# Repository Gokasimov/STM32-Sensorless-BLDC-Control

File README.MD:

# Sensorless BLDC Motor Controller (STM32G431RBT6)

## 📌 Overview
This repository contains the complete hardware and firmware design for a **Sensorless 6-Step Trapezoidal BLDC Motor Controller** built around the STM32G4 microcontroller. The project demonstrates advanced embedded motor control techniques, including Back-EMF (BEMF) Zero-Crossing Detection (ZCD) via Injected ADCs, hardware-synchronized timers, and a custom-tuned PI speed controller.

The hardware was designed from scratch (KiCad) and tested rigorously to evaluate both physical limits (Voltage Saturation/Kv limits) and embedded software constraints (Timer Quantization limits).

---

## ⚙️ Firmware Architecture & Control Theory

The firmware avoids blocking delays and polling. It relies entirely on a deterministic, interrupt-driven architecture utilizing STM32 Advanced Timers and ADC peripherals.

### 1. Robust State-Machine
The motor control flow is managed by a strict state machine to ensure safe start-up and running conditions:
* **IDLE:** PWM outputs are disabled (Soft Stop / Coasting).
* **ALIGN:** A static DC magnetic field is applied to the stator to force the mechanical rotor into a known starting position.
* **RAMP-UP:** Open-loop commutation with progressively decreasing delay to generate enough initial BEMF for the ADCs to read.
* **CLOSED-LOOP:** Sensorless commutation takes over. The system relies purely on ZCD events and the PI controller manages the PWM duty cycle to reach the target RPM.
* **FAULT:** Emergency hard-stop triggered by stall detection or hardware limits.

### 2. Injected ADC & Timer Synchronization
To avoid high-frequency PWM switching noise (ringing), BEMF is **not** polled continuously in the main loop. Instead, the STM32's **Injected ADC** channels are hardware-triggered by `TIM1`'s Update/Compare events. 
This ensures that the BEMF voltage is sampled exactly at the optimal moment (typically the PWM ON state or center-aligned peak), providing a clean signal for the ZCD algorithm without requiring heavy software filtering.

### 3. PI Speed Control & Super-Sampling (MAF)
Speed calculation at high RPMs suffers from timer resolution limits (Quantization Error). To mitigate this without using floating-point math on every cycle, a **Moving Average Filter (MAF)** is implemented.
The PI controller runs deterministically in a dedicated 1kHz timer interrupt (`TIM7`). It compares the filtered RPM against the target and smoothly adjusts the duty cycle, featuring anti-windup clamping to protect the system.

---

## 🔬 Key Hardware Verifications

Theoretical models were strictly validated against physical hardware behavior using a 4-channel oscilloscope and RAM data logging. *(For full oscilloscope captures, including Dead-Time verification, please see the [Results/](./Results) folder).*

### 1. Hardware RC Filter Phase Shift & ZCD Smoothing

> **Analysis:** The Yellow trace shows the raw Phase 1 voltage. The Blue trace shows the signal at the STM32 ADC pin after the resistor divider and RC filter. The filter successfully eliminates PWM noise. Crucially, the inherent RC time delay acts as a natural "Phase Advance," optimizing high-speed commutation timing directly in hardware, eliminating the need for 30-degree software compensation.

### 2. System Limit Discovery (RAM Datalogging)

> **Analysis (Step Response & Limitations):** Extracted via an 8KB internal RAM "Flight Recorder" to avoid UART bottlenecking. The graph reveals two physical realities:
> * **Voltage Saturation:** The PI controller pushes the Duty Cycle (Green) to its ~95% limit to reach 14200 RPM, but the motor plateaus at ~9500 RPM (Orange). The motor has hit its BEMF ceiling for a 12V supply ($\Delta V \approx 0$).
> * **Quantization Artifacts:** The step-like jumps at peak speeds are not physical. They are artifacts of the 50us timer resolution; at extreme speeds, a 1-tick variation in commutation measurement results in massive calculated RPM swings, proving the necessity of the MAF implemented in the code.

---

## 🔌 Quick Start & Hardware Setup

### Custom Hardware Notes (v1.0 Prototyping)
* **MP1482 Bypass:** Due to a layout errata on the v1.0 PCB, the onboard 12V-to-3.3V buck converter is bypassed. Logic power is supplied externally. (See `Hardware/ERRATA.md` for details).
* **Future-Proofing (DNP):** The board includes footprints for inline current shunts, op-amps, and encoder headers. These are currently marked as DNP (Do Not Populate) as they are reserved for the upcoming FOC (Field Oriented Control) revision.

## 📁 Repository Structure

📦 STM32-Sensorless-BLDC-Control
 ┣ 📂 Firmware         # STM32CubeIDE Project (C source, headers, .ioc)
 ┣ 📂 Hardware         # KiCad project, Schematics (PDF), BOM, and Errata
 ┣ 📂 Results          # Oscilloscope captures and Step Response graphs
 ┣ 📜 .gitignore       # Excludes IDE debug/build binaries
 ┣ 📜 README.md        # You are here
 ┗ 📜 LICENSE          # MIT License

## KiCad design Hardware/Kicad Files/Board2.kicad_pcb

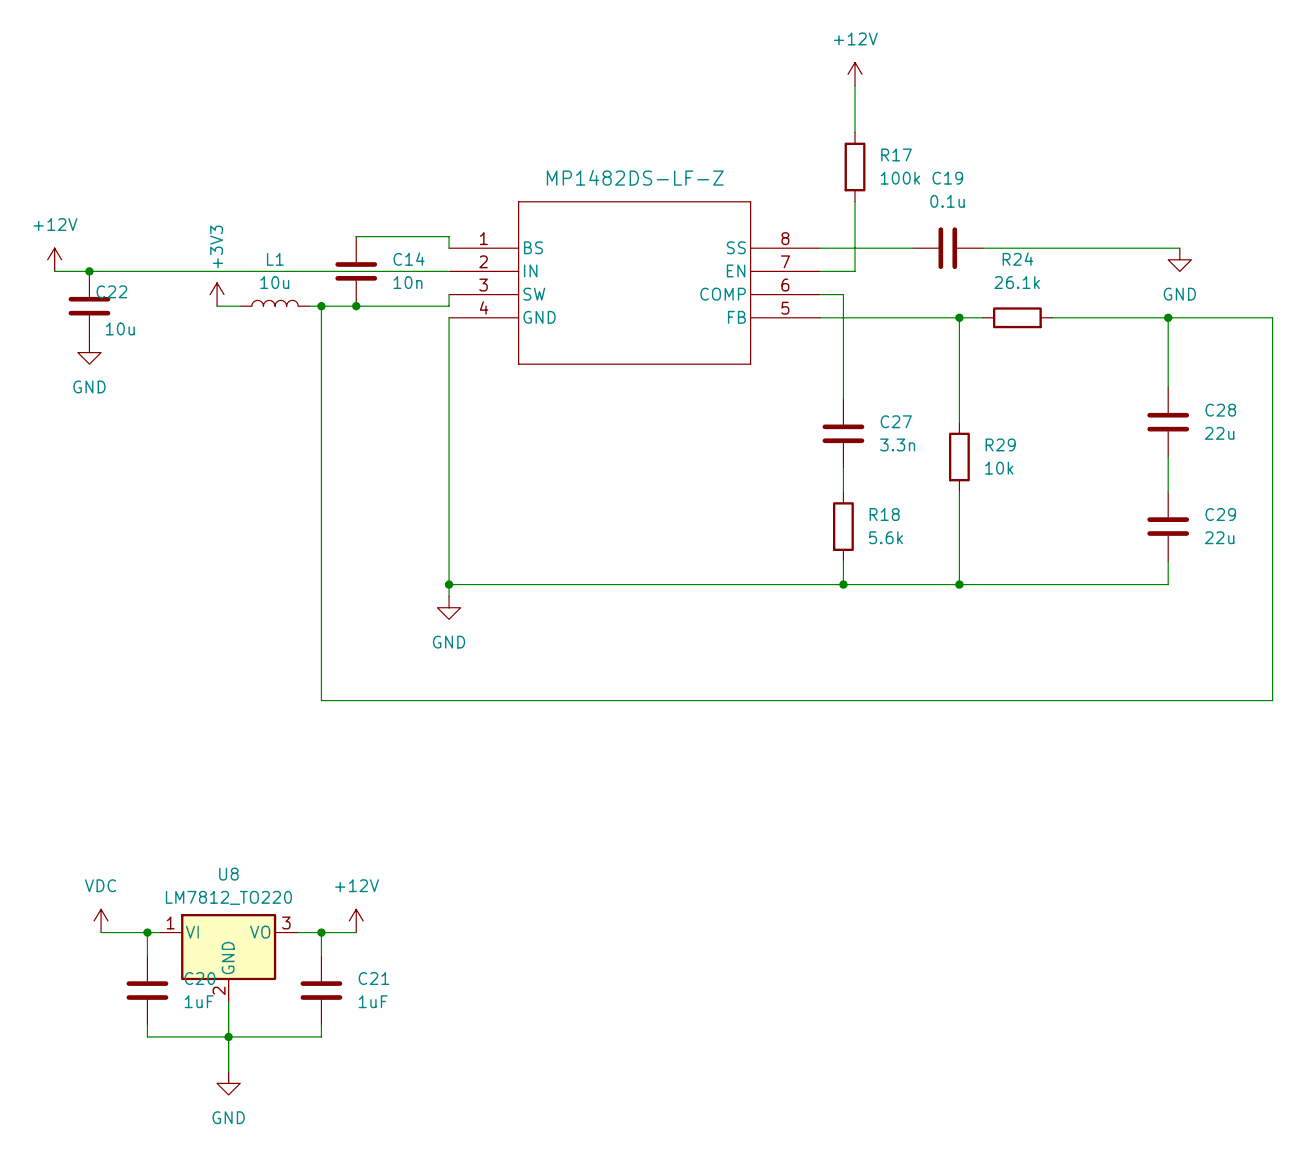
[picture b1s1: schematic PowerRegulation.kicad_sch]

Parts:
C14: 10n; C_0805_2012Metric
C19: 0.1u; C_0805_2012Metric
C20, C21: 1uF; C_0805_2012Metric
C22: 10u; C_0805_2012Metric
C27: 3.3n; C_0805_2012Metric
C28, C29: 22u; C_0805_2012Metric
L1: 10u; L_7.3x7.3_H3.5
R17: 100k; R_0805_2012Metric
R18: 5.6k; R_0805_2012Metric
R24: 26.1k; R_0805_2012Metric
R29: 10k; R_0805_2012Metric
U7: MP1482DS-LF-Z; SOIC-8_3.9x4.9mm_P1.27mm
U8: LM7812_TO220; TO-220-3_Vertical

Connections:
+3V3: L1.1; also elsewhere on the board
+12V: C21.1, C22.2, R17.1, U7.2 (IN), U8.3 (VO); also elsewhere on the board
GND: C19.2, C20.2, C21.2, C22.1, C29.1, R18.2, R29.2, U7.4 (GND), U8.2 (GND); also elsewhere on the board
unnamed: C27.1, R18.1
unnamed: C28.1, C29.2
unnamed: C14.1, U7.1 (BS)
unnamed: C27.2, U7.6 (COMP)
unnamed: R17.2, U7.7 (EN)
unnamed: R24.1, R29.1, U7.5 (FB)
unnamed: C19.1, U7.8 (SS)
unnamed: C14.2, C28.2, L1.2, R24.2, U7.3 (SW)
VDC: C20.1, U8.1 (VI); also elsewhere on the board

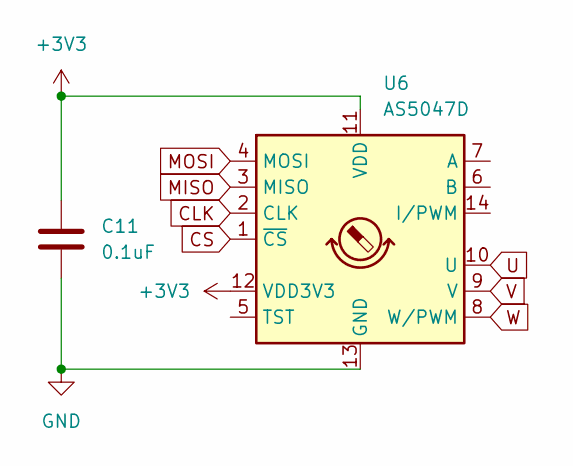
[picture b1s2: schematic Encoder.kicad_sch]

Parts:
C11: 0.1uF; C_0805_2012Metric
U6: AS5047D; TSSOP-14_4.4x5mm_P0.65mm

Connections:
+3V3: C11.1, U6.11 (VDD), U6.12 (VDD3V3); also elsewhere on the board
CLK: U6.2 (CLK); also elsewhere on the board
CS: U6.1 (~CS); also elsewhere on the board
GND: C11.2, U6.13 (GND); also elsewhere on the board
MISO: U6.3 (MISO); also elsewhere on the board
MOSI: U6.4 (MOSI); also elsewhere on the board
U: U6.10 (U); also elsewhere on the board
V: U6.9 (V); also elsewhere on the board
W: U6.8 (W/PWM); also elsewhere on the board

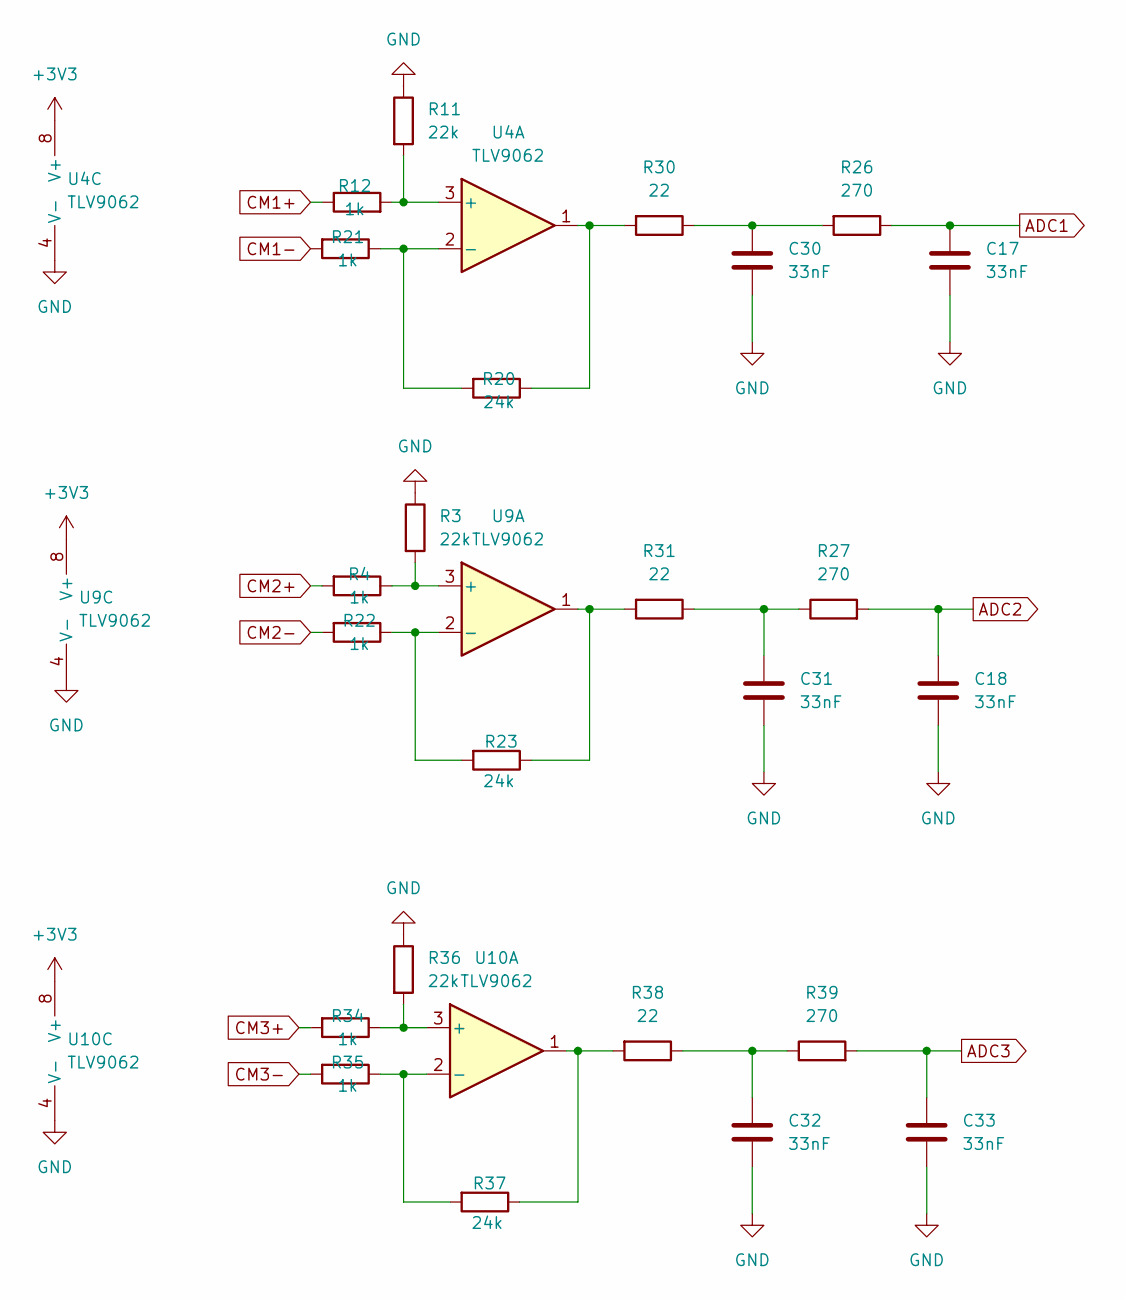
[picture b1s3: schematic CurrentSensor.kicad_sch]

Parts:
C17, C18, C30, C31, C32, C33: 33nF; C_0805_2012Metric
R3, R11, R36: 22k; R_0805_2012Metric
R4, R12, R21, R22, R34, R35: 1k; R_0805_2012Metric
R20, R23, R37: 24k; R_0805_2012Metric
R26, R27, R39: 270; R_0805_2012Metric
R30, R31, R38: 22; R_0805_2012Metric
U4, U9, U10: TLV9062; SOIC-8_3.9x4.9mm_P1.27mm

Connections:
+3V3: U4.8 (V+), U9.8 (V+), U10.8 (V+); also elsewhere on the board
ADC1: C17.1, R26.1; also elsewhere on the board
ADC2: C18.2, R27.2; also elsewhere on the board
ADC3: C33.2, R39.2
CM1+: R12.1; also elsewhere on the board
CM1-: R21.2; also elsewhere on the board
CM2+: R4.2; also elsewhere on the board
CM2-: R22.2; also elsewhere on the board
CM3+: R34.2; also elsewhere on the board
CM3-: R35.2; also elsewhere on the board
GND: C17.2, C18.1, C30.2, C31.2, C32.2, C33.1, R3.1, R11.1, R36.1, U4.4 (V-), U9.4 (V-), U10.4 (V-); also elsewhere on the board
unnamed: C30.1, R26.2, R30.1
unnamed: C31.1, R27.1, R31.1
unnamed: C32.1, R38.1, R39.1
unnamed: R20.1, R30.2, U4.1
unnamed: R23.1, R31.2, U9.1
unnamed: R37.1, R38.2, U10.1
unnamed: R11.2, R12.2, U4.3 (+)
unnamed: R20.2, R21.1, U4.2 (-)
unnamed: R3.2, R4.1, U9.3 (+)
unnamed: R22.1, R23.2, U9.2 (-)
unnamed: R34.1, R36.2, U10.3 (+)
unnamed: R35.1, R37.2, U10.2 (-)

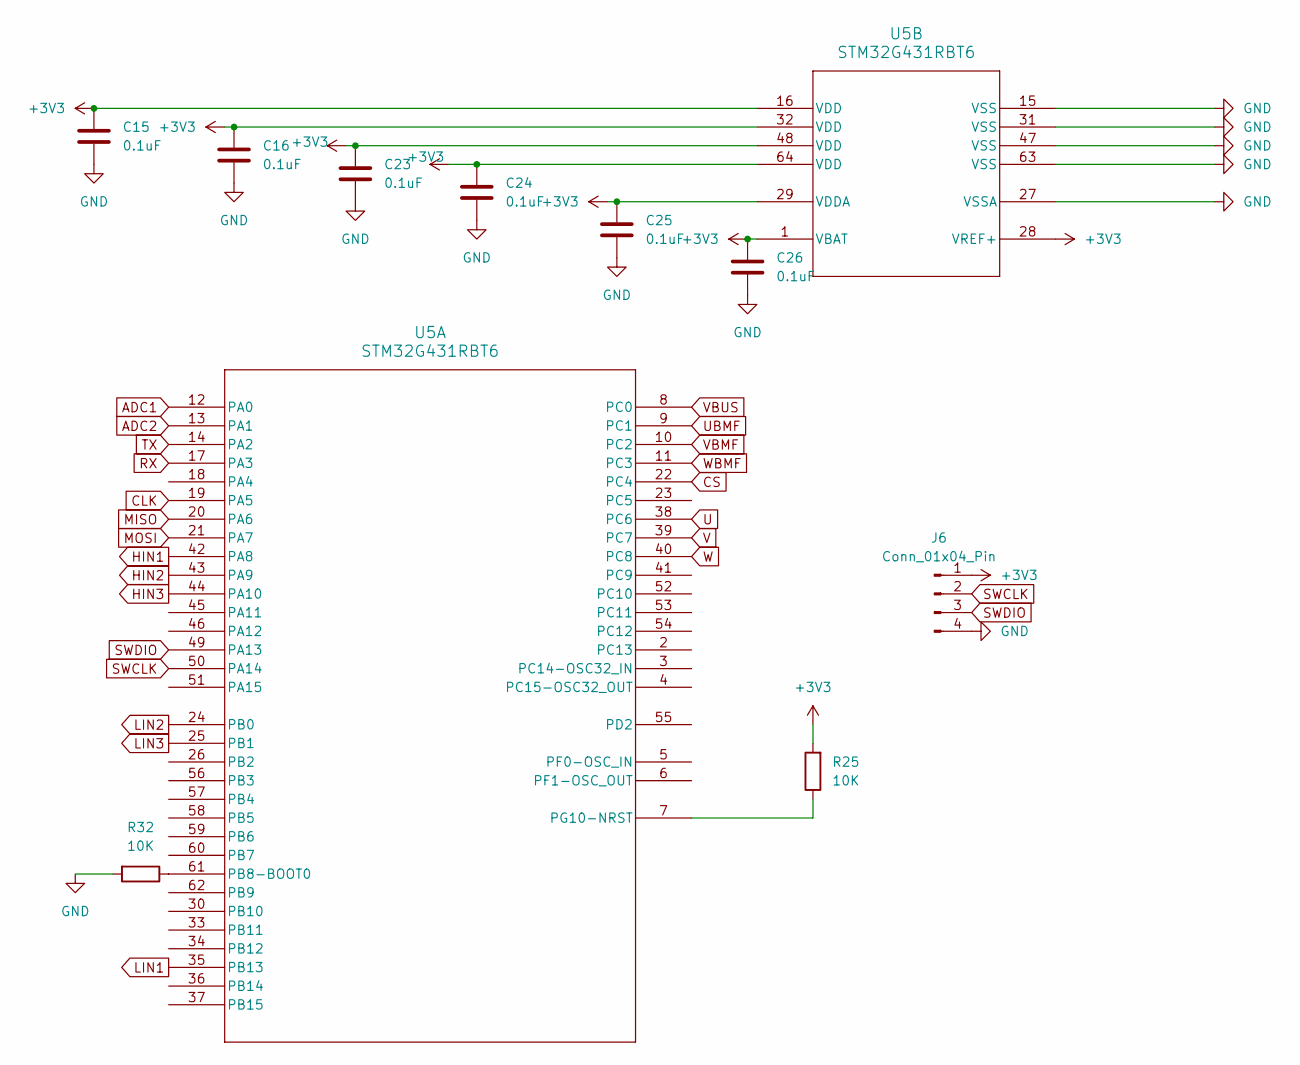
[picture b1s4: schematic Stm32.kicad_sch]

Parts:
C15, C16, C23, C24, C25, C26: 0.1uF; C_0805_2012Metric
J6: Conn_01x04_Pin; PinHeader_1x04_P2.54mm_Vertical
R25, R32: 10K; R_0805_2012Metric
U5: STM32G431RBT6; LQFP-64_10x10mm_P0.5mm

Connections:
+3V3: C15.1, C16.1, C23.1, C24.1, C25.1, C26.1, J6.1, R25.2, U5.1 (VBAT), U5.16 (VDD), U5.28 (VREF+), U5.29 (VDDA), U5.32 (VDD), U5.48 (VDD), U5.64 (VDD); also elsewhere on the board
ADC1: U5.12 (PA0); also elsewhere on the board
ADC2: U5.13 (PA1); also elsewhere on the board
CLK: U5.19 (PA5); also elsewhere on the board
CS: U5.22 (PC4); also elsewhere on the board
GND: C15.2, C16.2, C23.2, C24.2, C25.2, C26.2, J6.4, R32.2, U5.15 (VSS), U5.27 (VSSA), U5.31 (VSS), U5.47 (VSS), U5.63 (VSS); also elsewhere on the board
HIN1: U5.42 (PA8); also elsewhere on the board
HIN2: U5.43 (PA9); also elsewhere on the board
HIN3: U5.44 (PA10); also elsewhere on the board
LIN1: U5.35 (PB13); also elsewhere on the board
LIN2: U5.24 (PB0); also elsewhere on the board
LIN3: U5.25 (PB1); also elsewhere on the board
MISO: U5.20 (PA6); also elsewhere on the board
MOSI: U5.21 (PA7); also elsewhere on the board
unnamed: R32.1, U5.61 (PB8-BOOT0)
unnamed: R25.1, U5.7 (PG10-NRST)
RX: U5.17 (PA3)
SWCLK: J6.2, U5.50 (PA14)
SWDIO: J6.3, U5.49 (PA13)
TX: U5.14 (PA2)
U: U5.38 (PC6); also elsewhere on the board
UBMF: U5.9 (PC1); also elsewhere on the board
V: U5.39 (PC7); also elsewhere on the board
VBMF: U5.10 (PC2); also elsewhere on the board
VBUS: U5.8 (PC0); also elsewhere on the board
W: U5.40 (PC8); also elsewhere on the board
WBMF: U5.11 (PC3); also elsewhere on the board

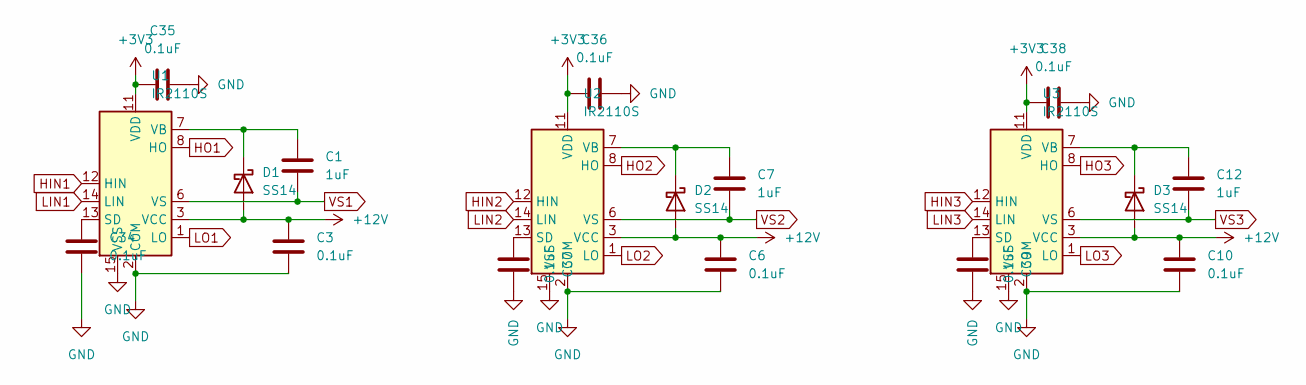
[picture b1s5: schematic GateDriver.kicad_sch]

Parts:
C1, C7, C12: 1uF; C_0805_2012Metric
C3, C6, C10, C34, C35, C36, C37, C38, C39: 0.1uF; C_0805_2012Metric
D1, D2, D3: SS14; D_SMA
U1, U2, U3: IR2110S; SOIC-16W_7.5x10.3mm_P1.27mm

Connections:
+3V3: C35.1, C36.1, C38.1, U1.11 (VDD), U2.11 (VDD), U3.11 (VDD); also elsewhere on the board
+12V: C3.1, C6.1, C10.1, D1.2 (A), D2.2 (A), D3.2 (A), U1.3 (VCC), U2.3 (VCC), U3.3 (VCC); also elsewhere on the board
GND: C3.2, C6.2, C10.2, C34.2, C35.2, C36.2, C37.2, C38.2, C39.2, U1.2 (COM), U1.15 (VSS), U2.2 (COM), U2.15 (VSS), U3.2 (COM), U3.15 (VSS); also elsewhere on the board
HIN1: U1.12 (HIN); also elsewhere on the board
HIN2: U2.12 (HIN); also elsewhere on the board
HIN3: U3.12 (HIN); also elsewhere on the board
HO1: U1.8 (HO); also elsewhere on the board
HO2: U2.8 (HO); also elsewhere on the board
HO3: U3.8 (HO); also elsewhere on the board
LIN1: U1.14 (LIN); also elsewhere on the board
LIN2: U2.14 (LIN); also elsewhere on the board
LIN3: U3.14 (LIN); also elsewhere on the board
LO1: U1.1 (LO); also elsewhere on the board
LO2: U2.1 (LO); also elsewhere on the board
LO3: U3.1 (LO); also elsewhere on the board
unnamed: C1.1, D1.1 (K), U1.7 (VB)
unnamed: C7.1, D2.1 (K), U2.7 (VB)
unnamed: C12.1, D3.1 (K), U3.7 (VB)
unnamed: C34.1, U1.13 (SD)
unnamed: C37.1, U2.13 (SD)
unnamed: C39.1, U3.13 (SD)
VS1: C1.2, U1.6 (VS); also elsewhere on the board
VS2: C7.2, U2.6 (VS); also elsewhere on the board
VS3: C12.2, U3.6 (VS); also elsewhere on the board

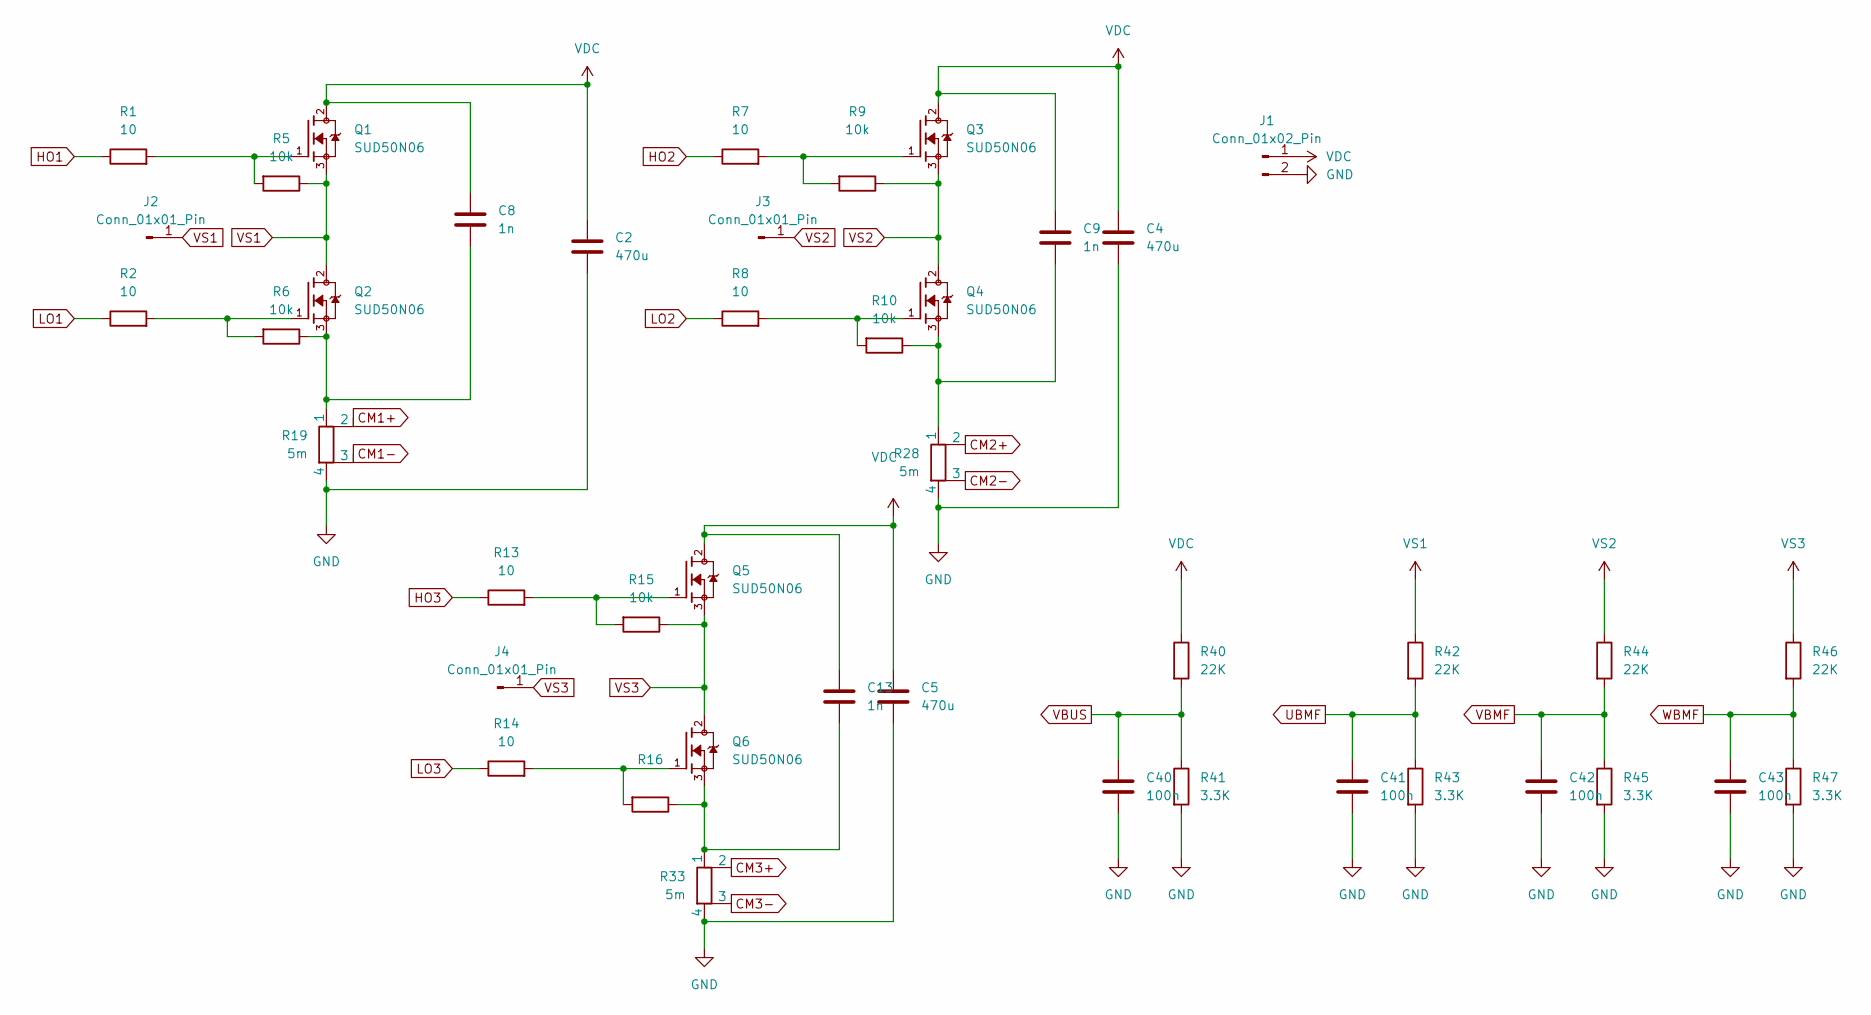
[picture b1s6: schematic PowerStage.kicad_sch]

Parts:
C2, C4, C5: 470u; CP_Radial_D10.0mm_P5.00mm
C8, C9, C13: 1n; C_0805_2012Metric
C40, C41, C42, C43: 100n; C_0805_2012Metric
J1: Conn_01x02_Pin; AMASS_XT60-M_1x02_P7.20mm_Vertical
J2, J3, J4: Conn_01x01_Pin; SolderWire-2sqmm_1x01_D2mm_OD3.9mm
Q1, Q2, Q3, Q4, Q5, Q6: SUD50N06; TO-252-2
R1, R2, R7, R8, R13, R14: 10; R_0805_2012Metric
R5, R6, R9, R10, R15, R16: 10k; R_0805_2012Metric
R19, R28, R33: 5m; R_Shunt_Vishay_WSK2512_6332Metric_T1.19mm
R40, R42, R44, R46: 22K; R_0805_2012Metric
R41, R43, R45, R47: 3.3K; R_0805_2012Metric

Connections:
CM1+: R19.2; also elsewhere on the board
CM1-: R19.3; also elsewhere on the board
CM2+: R28.2; also elsewhere on the board
CM2-: R28.3; also elsewhere on the board
CM3+: R33.2; also elsewhere on the board
CM3-: R33.3; also elsewhere on the board
GND: C2.2, C4.2, C5.2, C40.2, C41.2, C42.2, C43.2, J1.2, R19.4, R28.4, R33.4, R41.2, R43.2, R45.2, R47.2; also elsewhere on the board
HO1: R1.1; also elsewhere on the board
HO2: R7.1; also elsewhere on the board
HO3: R13.1; also elsewhere on the board
LO1: R2.1; also elsewhere on the board
LO2: R8.1; also elsewhere on the board
LO3: R14.1; also elsewhere on the board
unnamed: C8.2, Q2.3, R6.1, R19.1
unnamed: C9.2, Q4.3, R10.1, R28.1
unnamed: C13.2, Q6.3, R16.1, R33.1
unnamed: Q1.1, R1.2, R5.2
unnamed: Q2.1, R2.2, R6.2
unnamed: Q3.1, R7.2, R9.2
unnamed: Q4.1, R8.2, R10.2
unnamed: Q5.1, R13.2, R15.2
unnamed: Q6.1, R14.2, R16.2
UBMF: C41.1, R42.2, R43.1; also elsewhere on the board
VBMF: C42.1, R44.2, R45.1; also elsewhere on the board
VBUS: C40.1, R40.2, R41.1; also elsewhere on the board
VDC: C2.1, C4.1, C5.1, C8.1, C9.1, C13.1, J1.1, Q1.2, Q3.2, Q5.2, R40.1; also elsewhere on the board
VS1: J2.1, Q1.3, Q2.2, R5.1, R42.1; also elsewhere on the board
VS2: J3.1, Q3.3, Q4.2, R9.1, R44.1; also elsewhere on the board
VS3: J4.1, Q5.3, Q6.2, R15.1, R46.1; also elsewhere on the board
WBMF: C43.1, R46.2, R47.1; also elsewhere on the board

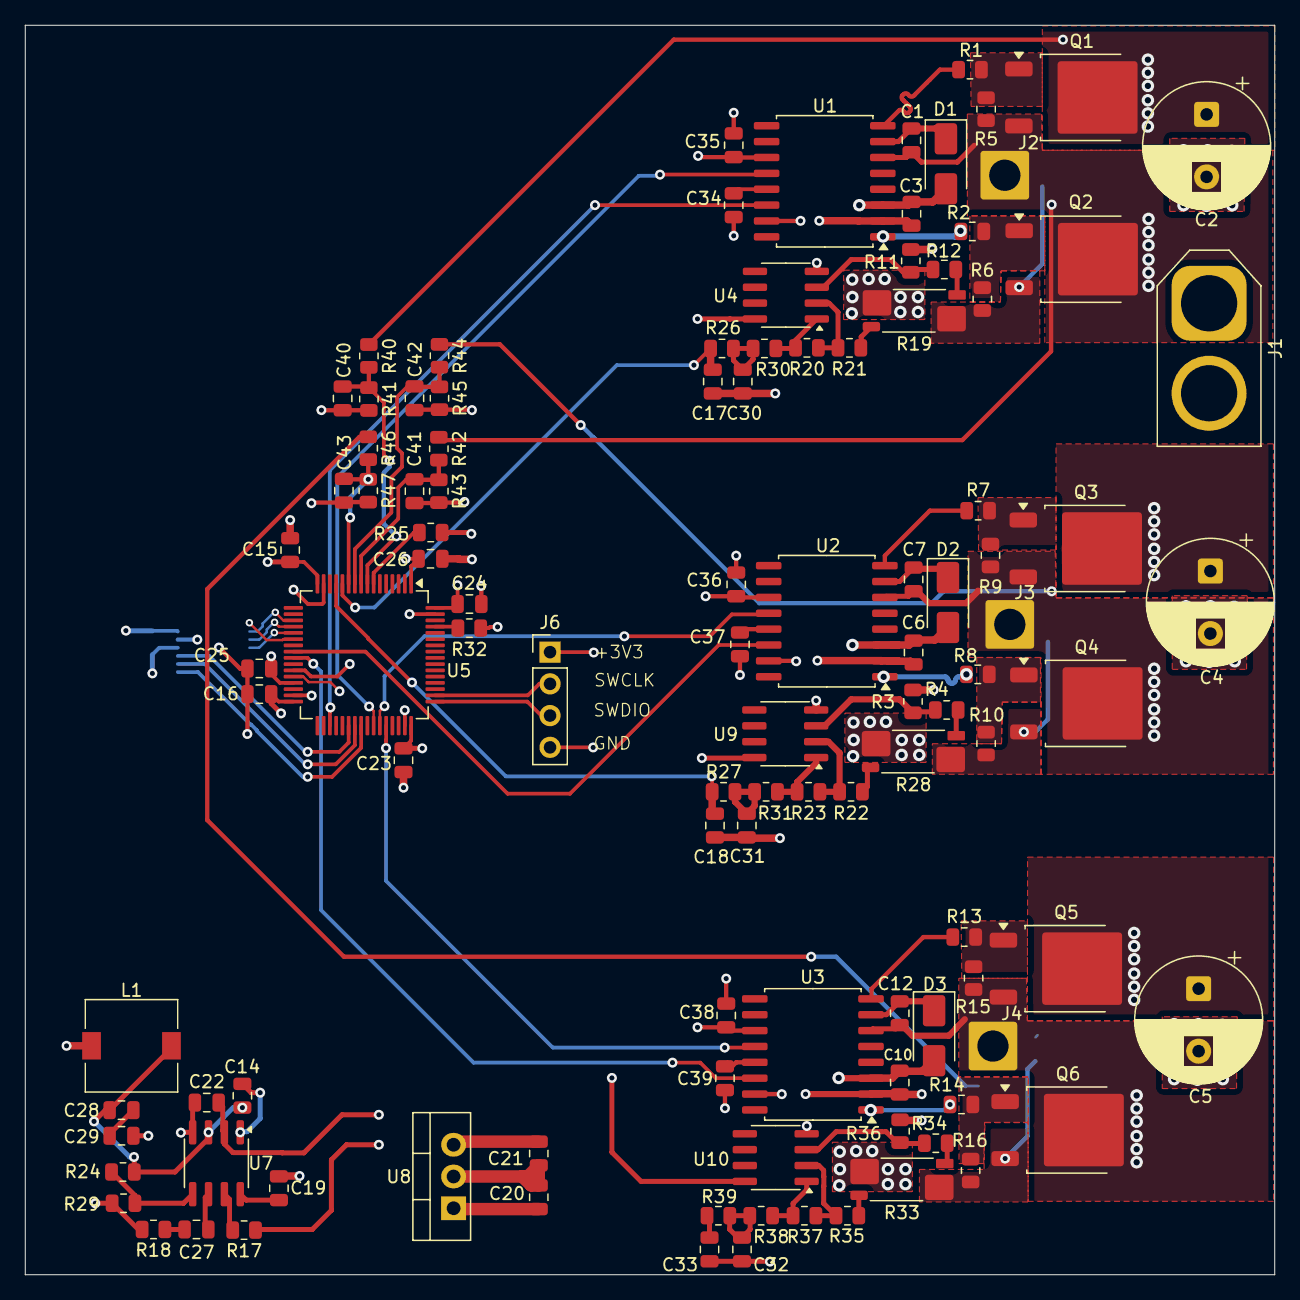
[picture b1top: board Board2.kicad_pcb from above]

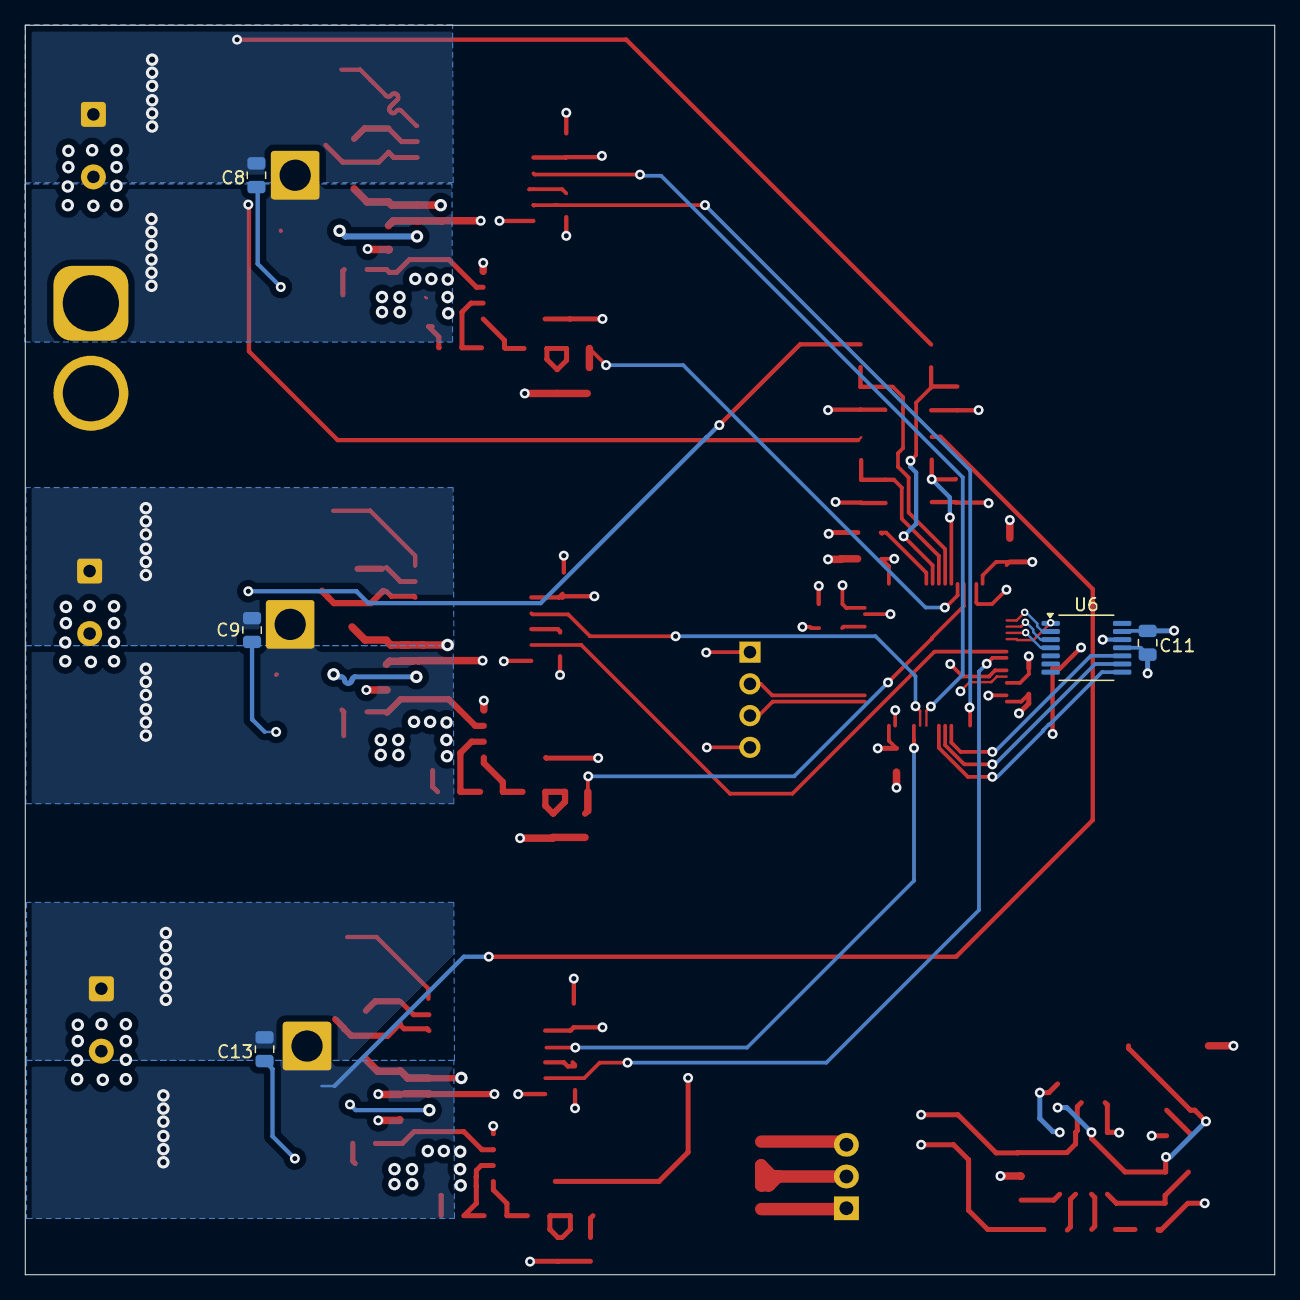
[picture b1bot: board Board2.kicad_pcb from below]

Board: 4 copper layers, 100.0 x 100.0 mm, 115 parts (5 on the bottom side), 78 nets.

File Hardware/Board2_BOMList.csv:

Reference,Qty,Value,Footprint,
"C1,C7,C12,C20,C21",5,1uF,Capacitor_SMD:C_0805_2012Metric,
"C2,C4,C5",3,470u,Capacitor_THT:CP_Radial_D10.0mm_P5.00mm,
"C3,C6,C10,C11,C15,C16,C23,C24,C25,C26,C34,C35,C36,C37,C38,C39",16,0.1uF,Capacitor_SMD:C_0805_2012Metric,
"C8,C9,C13",3,1n,Capacitor_SMD:C_0805_2012Metric,
C14,1,10n,Capacitor_SMD:C_0805_2012Metric,
"C17,C18,C30,C31,C32,C33",6,33nF,Capacitor_SMD:C_0805_2012Metric,
C19,1,0.1u,Capacitor_SMD:C_0805_2012Metric,
C22,1,10u,Capacitor_SMD:C_0805_2012Metric,
C27,1,3.3n,Capacitor_SMD:C_0805_2012Metric,
"C28,C29",2,22n,Capacitor_SMD:C_0805_2012Metric,
"C40,C41,C42,C43",4,100n,Capacitor_SMD:C_0805_2012Metric,
"D1,D2,D3",3,SS14,Diode_SMD:D_SMA,
J1,1,Conn_01x02_Pin,Connector_AMASS:AMASS_XT60-F_1x02_P7.20mm_Vertical,
"J2,J3,J4",3,Conn_01x01_Pin,Connector_Wire:SolderWire-2sqmm_1x01_D2mm_OD3.9mm,
J6,1,Conn_01x04_Pin,Connector_PinHeader_2.54mm:PinHeader_1x04_P2.54mm_Vertical,
L1,1,10u,Inductor_SMD:L_7.3x7.3_H3.5,
"Q1,Q2,Q3,Q4,Q5,Q6",6,panjit-pjd80n06sa-au,Package_TO_SOT_SMD:TO-252-2,
"R1,R2,R7,R8,R13,R14",6,10,Resistor_SMD:R_0805_2012Metric,
"R3,R11,R36",3,22k,Resistor_SMD:R_0805_2012Metric,
"R4,R12,R21,R22,R34,R35",6,1k,Resistor_SMD:R_0805_2012Metric,
"R5,R6,R9,R10,R15,R16,R29",7,10k,Resistor_SMD:R_0805_2012Metric,
R17,1,100k,Resistor_SMD:R_0805_2012Metric,
R18,1,5.6k,Resistor_SMD:R_0805_2012Metric,
"R19,R28,R33",3,5m,Resistor_SMD:R_Shunt_Vishay_WSK2512_6332Metric_T1.19mm,
"R20,R23,R37",3,24k,Resistor_SMD:R_0805_2012Metric,
R24,1,26.1k,Resistor_SMD:R_0805_2012Metric,
"R25,R32",2,10K,Resistor_SMD:R_0805_2012Metric,
"R26,R27,R39",3,270,Resistor_SMD:R_0805_2012Metric,
"R30,R31,R38",3,22,Resistor_SMD:R_0805_2012Metric,
"R40,R42,R44,R46",4,22K,Resistor_SMD:R_0805_2012Metric,
"R41,R43,R45,R47",4,3.3K,Resistor_SMD:R_0805_2012Metric,
"U1,U2,U3",3,IR2110S,Package_SO:SOIC-16W_7.5x10.3mm_P1.27mm,
"U4,U9,U10",3,TLV9062,Package_SO:SOIC-8_3.9x4.9mm_P1.27mm,DNP
U5,1,STM32G431RBT6,Package_QFP:LQFP-64_10x10mm_P0.5mm,
U6,1,AS5047D,Package_SO:TSSOP-14_4.4x5mm_P0.65mm,DNP
U7,1,MP1482DS-LF-Z,Package_SO:SOIC-8_3.9x4.9mm_P1.27mm,
U8,1,LM7812_TO220,Package_TO_SOT_THT:TO-220-3_Vertical,

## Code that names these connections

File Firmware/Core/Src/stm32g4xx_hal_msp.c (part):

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
    __HAL_RCC_GPIOC_CLK_ENABLE();
    /**ADC1 GPIO Configuration
    PC0     ------> ADC1_IN6
    PC1     ------> ADC1_IN7
    PC2     ------> ADC1_IN8
    PC3     ------> ADC1_IN9
    */
    GPIO_InitStruct.Pin = GPIO_PIN_0|GPIO_PIN_1|GPIO_PIN_2|GPIO_PIN_3;
    GPIO_InitStruct.Mode = GPIO_MODE_ANALOG;
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    __HAL_RCC_ADC12_CLK_DISABLE();

    /**ADC1 GPIO Configuration
    PC0     ------> ADC1_IN6
    PC1     ------> ADC1_IN7
    PC2     ------> ADC1_IN8
    PC3     ------> ADC1_IN9
    */
    HAL_GPIO_DeInit(GPIOC, GPIO_PIN_0|GPIO_PIN_1|GPIO_PIN_2|GPIO_PIN_3);

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    __HAL_RCC_GPIOB_CLK_ENABLE();
    __HAL_RCC_GPIOA_CLK_ENABLE();
    /**TIM1 GPIO Configuration
    PB0     ------> TIM1_CH2N
    PB1     ------> TIM1_CH3N
    PB13     ------> TIM1_CH1N
    PA8     ------> TIM1_CH1
    PA9     ------> TIM1_CH2
    PA10     ------> TIM1_CH3
    */
    GPIO_InitStruct.Pin = GPIO_PIN_0|GPIO_PIN_1|GPIO_PIN_13;
    GPIO_InitStruct.Mode = GPIO_MODE_AF_PP;
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
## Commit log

2026-03-15 Initial commit: v1.0 Sensorless BLDC Controller (Firmware, Hardware, Results)
    Added complete KiCad hardware design files, STM32CubeIDE firmware with PI speed control & ZCD, and oscilloscope verification results. Project is ready for v1.0 release.

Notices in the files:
Firmware/Core/Src/stm32g4xx_hal_msp.c:
Copyright (c) 2026 STMicroelectronics.
All rights reserved.
This software is licensed under terms that can be found in the LICENSE file
